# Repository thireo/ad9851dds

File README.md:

# ad9851dds
VFO based on AD9851 for future use in homemade RF Receiver
Branch testing

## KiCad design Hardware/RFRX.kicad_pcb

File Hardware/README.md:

# ad9851dds
VFO based on AD9851 for future use in homemade RF Receiver
Branch testing
revision 2 branch test?

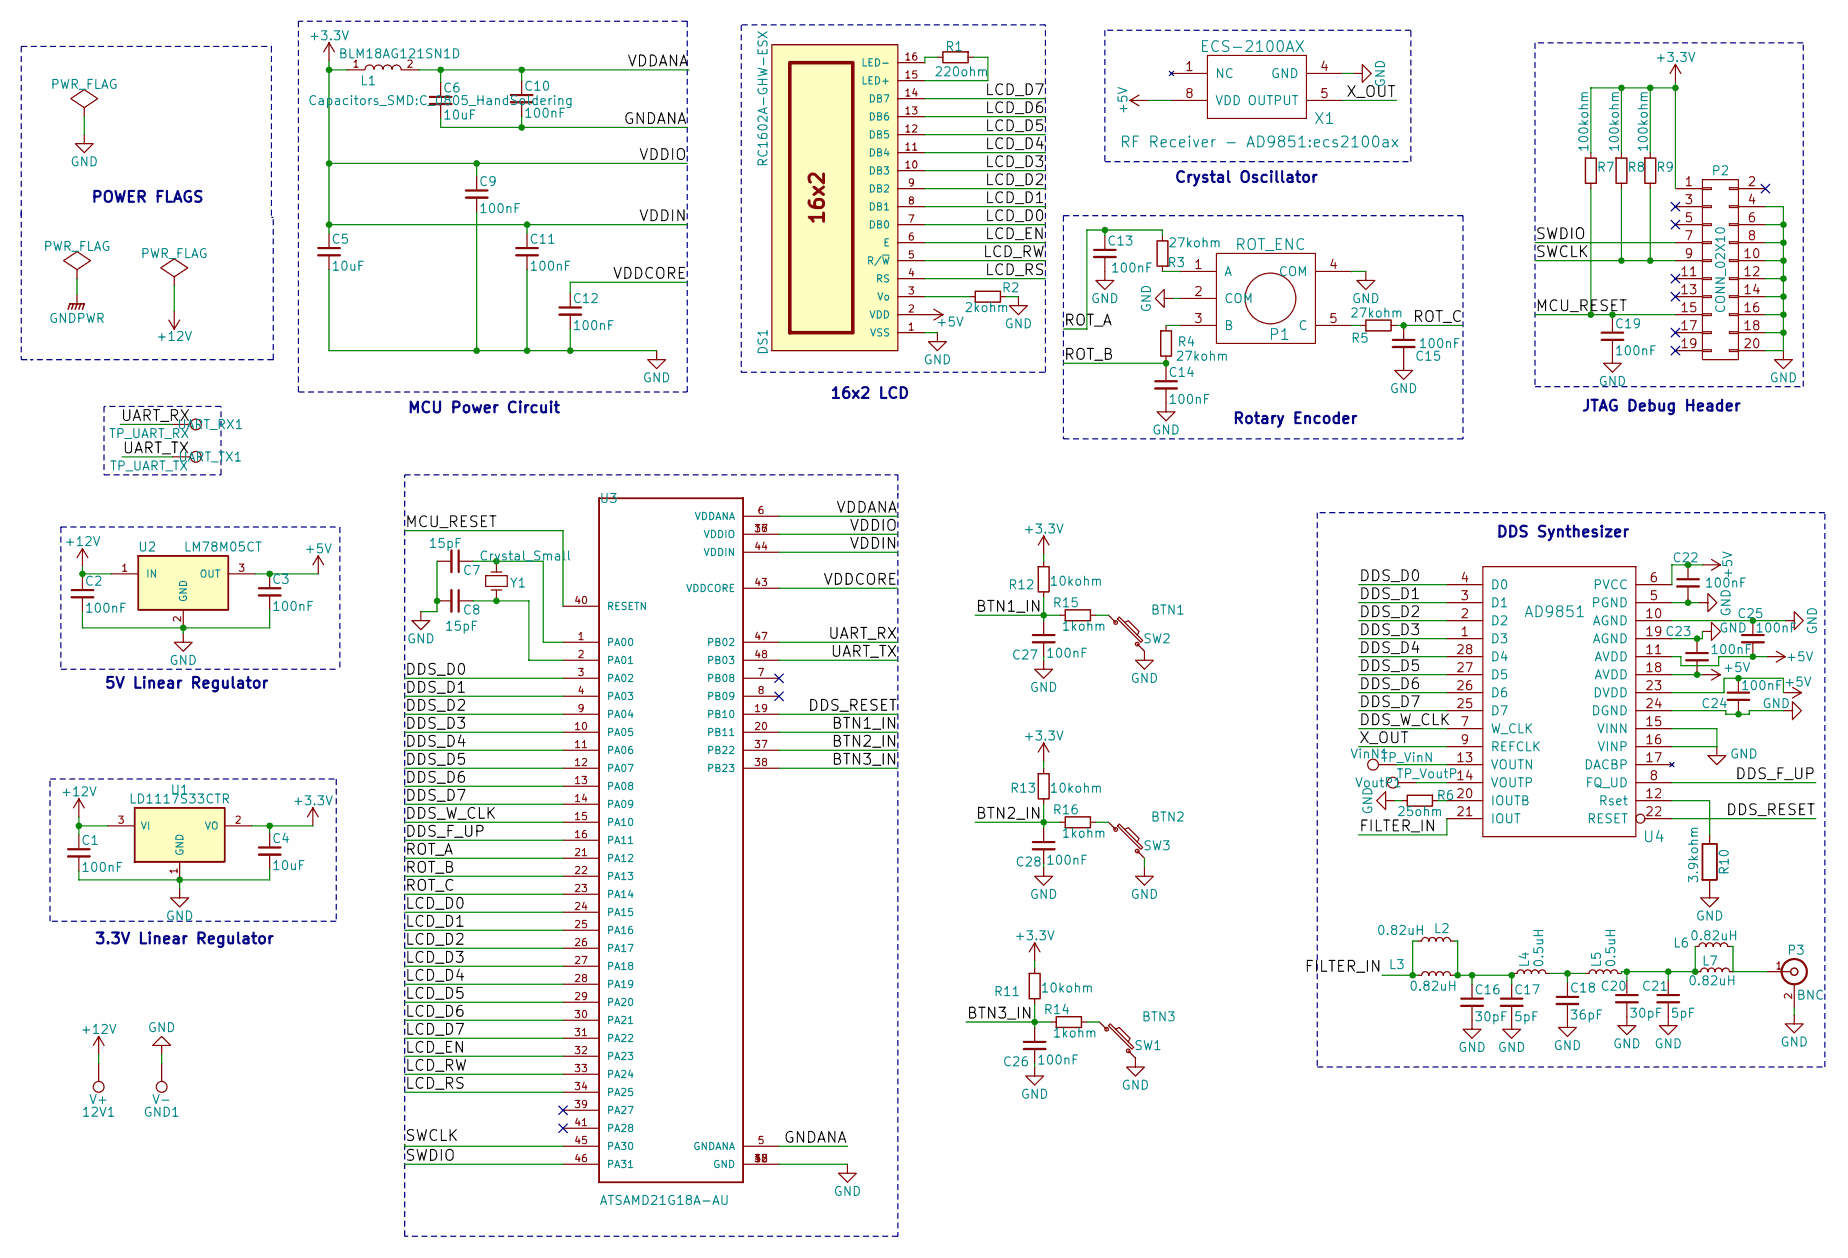
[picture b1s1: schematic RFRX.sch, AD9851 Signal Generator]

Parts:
12V1: V+; SolderWirePad_single_1-2mmDrill
C1, C2, C3, C9, C10, C11, C12, C13, C14, C15, C19, C22, C23, C24, C25, C26, C27, C28: 100nF; C_0805_HandSoldering
C4, C5, C6: 10uF; C_0805_HandSoldering
C7, C8: 15pF; C_0805_HandSoldering
C16, C20: 30pF; C_0805_HandSoldering
C17, C21: 5pF; C_0805_HandSoldering
C18: 36pF; C_0805_HandSoldering
DS1: RC1602A-GHW-ESX; Pin_Header_Straight_1x16
GND1: V-; SolderWirePad_single_1-2mmDrill
L1: BLM18AG121SN1D; R_1206_HandSoldering
L2, L3, L6, L7: 0.82uH; C_0603_HandSoldering
L4, L5: 0.5uH; C_0603_HandSoldering
P1: ROT_ENC; Pin_Header_Straight_1x05
P2: CONN_02X10; Pin_Header_Straight_2x10
P3: BNC; BNC_Socket_TYCO-AMP
R1: 220ohm; R_0805_HandSoldering
R2: 2kohm; R_0805_HandSoldering
R3, R4, R5: 27kohm; R_0805_HandSoldering
R6: 25ohm; R_0805_HandSoldering
R7, R8, R9: 100kohm; R_0805_HandSoldering
R10: 3.9kohm; R_0805_HandSoldering
R11, R12, R13: 10kohm; R_0805_HandSoldering
R14, R15, R16: 1kohm; R_0805_HandSoldering
SW1: BTN3; SolderWirePad_2x_1mmDrill
SW2: BTN1; SolderWirePad_2x_1mmDrill
SW3: BTN2; SolderWirePad_2x_1mmDrill
U1: LD1117S33CTR; SOT-223
U2: LM78M05CT; TO-220_Neutral123_Horizontal_LargePads
U3: ATSAMD21G18A-AU; TQFP-48_7x7mm_Pitch0.5mm
U4: AD9851; SSOP-28_5.3x10.2mm_Pitch0.65mm
UART_RX1: TP_UART_RX; SolderWirePad_single_1-2mmDrill
UART_TX1: TP_UART_TX; SolderWirePad_single_1-2mmDrill
VinN1: TP_VinN; SolderWirePad_single_1-2mmDrill
VoutP1: TP_VoutP; SolderWirePad_single_1-2mmDrill
X1: ECS-2100AX; ecs2100ax
Y1: Crystal_Small; XTAL320X150X90

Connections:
+3V3: C4.1, C5.1, C9.1, C11.1, L1.1, P2.1, R7.1, R8.1, R9.1, R11.1, R12.1, R13.1, U1.2 (VO), U3.17 (VDDIO), U3.36 (VDDIO), U3.44 (VDDIN)
+5V: C3.1, C22.1, C23.2, C24.1, C25.2, DS1.2 (VDD), U2.3 (OUT), U4.6 (PVCC), U4.11 (AVDD), U4.18 (AVDD), U4.23 (DVDD), X1.8 (VDD)
+12V: 12V1.1, C1.1, C2.1, U1.3 (VI), U2.1 (IN); also elsewhere on the board
/BTN1_IN: C27.1, R12.2, R15.1, U3.20 (PB11)
/BTN2_IN: C28.1, R13.2, R16.1, U3.37 (PB22)
/BTN3_IN: C26.1, R11.2, R14.1, U3.38 (PB23)
/DDS_D0: U3.3 (PA02), U4.4 (D0)
/DDS_D1: U3.4 (PA03), U4.3 (D1)
/DDS_D2: U3.9 (PA04), U4.2 (D2)
/DDS_D3: U3.10 (PA05), U4.1 (D3)
/DDS_D4: U3.11 (PA06), U4.28 (D4)
/DDS_D5: U3.12 (PA07), U4.27 (D5)
/DDS_D6: U3.13 (PA08), U4.26 (D6)
/DDS_D7: U3.14 (PA09), U4.25 (D7)
/DDS_F_UP: U3.16 (PA11), U4.8 (FQ_UD)
/DDS_RESET: U3.19 (PB10), U4.22 (RESET)
/DDS_W_CLK: U3.15 (PA10), U4.7 (W_CLK)
/FILTER_IN: L2.1, L3.1, U4.21 (IOUT)
/GNDANA: C6.2, C10.2, U3.5 (GNDANA)
/LCD_D0: DS1.7 (DB0), U3.24 (PA15)
/LCD_D1: DS1.8 (DB1), U3.25 (PA16)
/LCD_D2: DS1.9 (DB2), U3.26 (PA17)
/LCD_D3: DS1.10 (DB3), U3.27 (PA18)
/LCD_D4: DS1.11 (DB4), U3.28 (PA19)
/LCD_D5: DS1.12 (DB5), U3.29 (PA20)
/LCD_D6: DS1.13 (DB6), U3.30 (PA21)
/LCD_D7: DS1.14 (DB7), U3.31 (PA22)
/LCD_EN: DS1.6 (E), U3.32 (PA23)
/LCD_RS: DS1.4 (RS), U3.34 (PA25)
/LCD_RW: DS1.5 (R/~W), U3.33 (PA24)
/MCU_RESET: C19.1, P2.15, R7.2, U3.40 (RESETN)
/ROT_A: C13.1, R3.2, U3.21 (PA12)
/ROT_B: C14.1, R4.2, U3.22 (PA13)
/ROT_C: C15.1, R5.2, U3.23 (PA14)
/SWCLK: P2.9, R8.2, R9.2, U3.45 (PA30)
/SWDIO: P2.7, U3.46 (PA31)
/UART_RX: U3.47 (PB02), UART_RX1.1; also elsewhere on the board
/UART_TX: U3.48 (PB03), UART_TX1.1; also elsewhere on the board
/VDDANA: C6.1, C10.1, L1.2, U3.6 (VDDANA)
/VDDCORE: C12.1, U3.43 (VDDCORE)
/X_OUT: U4.9 (REFCLK), X1.5 (OUTPUT)
GND: C1.2, C2.2, C3.2, C4.2, C5.2, C7.2, C8.2, C9.2, C11.2, C12.2, C13.2, C14.2, C15.2, C16.2, C17.2, C18.2, C19.2, C20.2, C21.2, C22.2, C23.1, C24.2, C25.1, C26.2, C27.2, C28.2, DS1.1 (VSS), GND1.1, P1.2 (COM), P1.4 (COM), P2.4, P2.6, P2.8, P2.10, P2.12, P2.14, P2.16, P2.18, P2.20, P3.2 (Ext), R2.2, R6.2, R10.2, SW1.1, SW1.2, SW2.1, SW2.2, SW3.1, SW3.2, U1.1 (GND), U1.4, U2.2 (GND), U3.18 (GND), U3.35 (GND), U3.42 (GND), U4.5 (PGND), U4.10 (AGND), U4.15 (VINN), U4.16 (VINP), U4.19 (AGND), U4.24 (DGND), X1.4 (GND); also elsewhere on the board
unnamed: C7.1, U3.1 (PA00), Y1.1
unnamed: C8.1, U3.2 (PA01), Y1.2
unnamed: C16.1, C17.1, L2.2, L3.2, L4.1
unnamed: C18.1, L4.2, L5.1
unnamed: C20.1, C21.1, L5.2, L6.1, L7.1
unnamed: DS1.3 (Vo), R2.1
unnamed: DS1.15 (LED+), R1.1
unnamed: DS1.16 (LED-), R1.2
unnamed: L6.2, L7.2, P3.1 (In)
unnamed: P1.1 (A), R3.1
unnamed: P1.3 (B), R4.1
unnamed: P1.5 (C), R5.1
unnamed: R6.1, U4.20 (IOUTB)
unnamed: R10.1, U4.12 (Rset)
unnamed: R14.2, SW1.1
unnamed: R15.2, SW2.1
unnamed: R16.2, SW3.1
unnamed 70: U4.13 (VOUTN), VinN1.1; also elsewhere on the board
unnamed 71: U4.14 (VOUTP), VoutP1.1; also elsewhere on the board

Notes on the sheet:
DDS Synthesizer
Crystal Oscillator
16x2 LCD
MCU Power Circuit
POWER FLAGS
Rotary Encoder
JTAG Debug Header
3.3V Linear Regulator
5V Linear Regulator

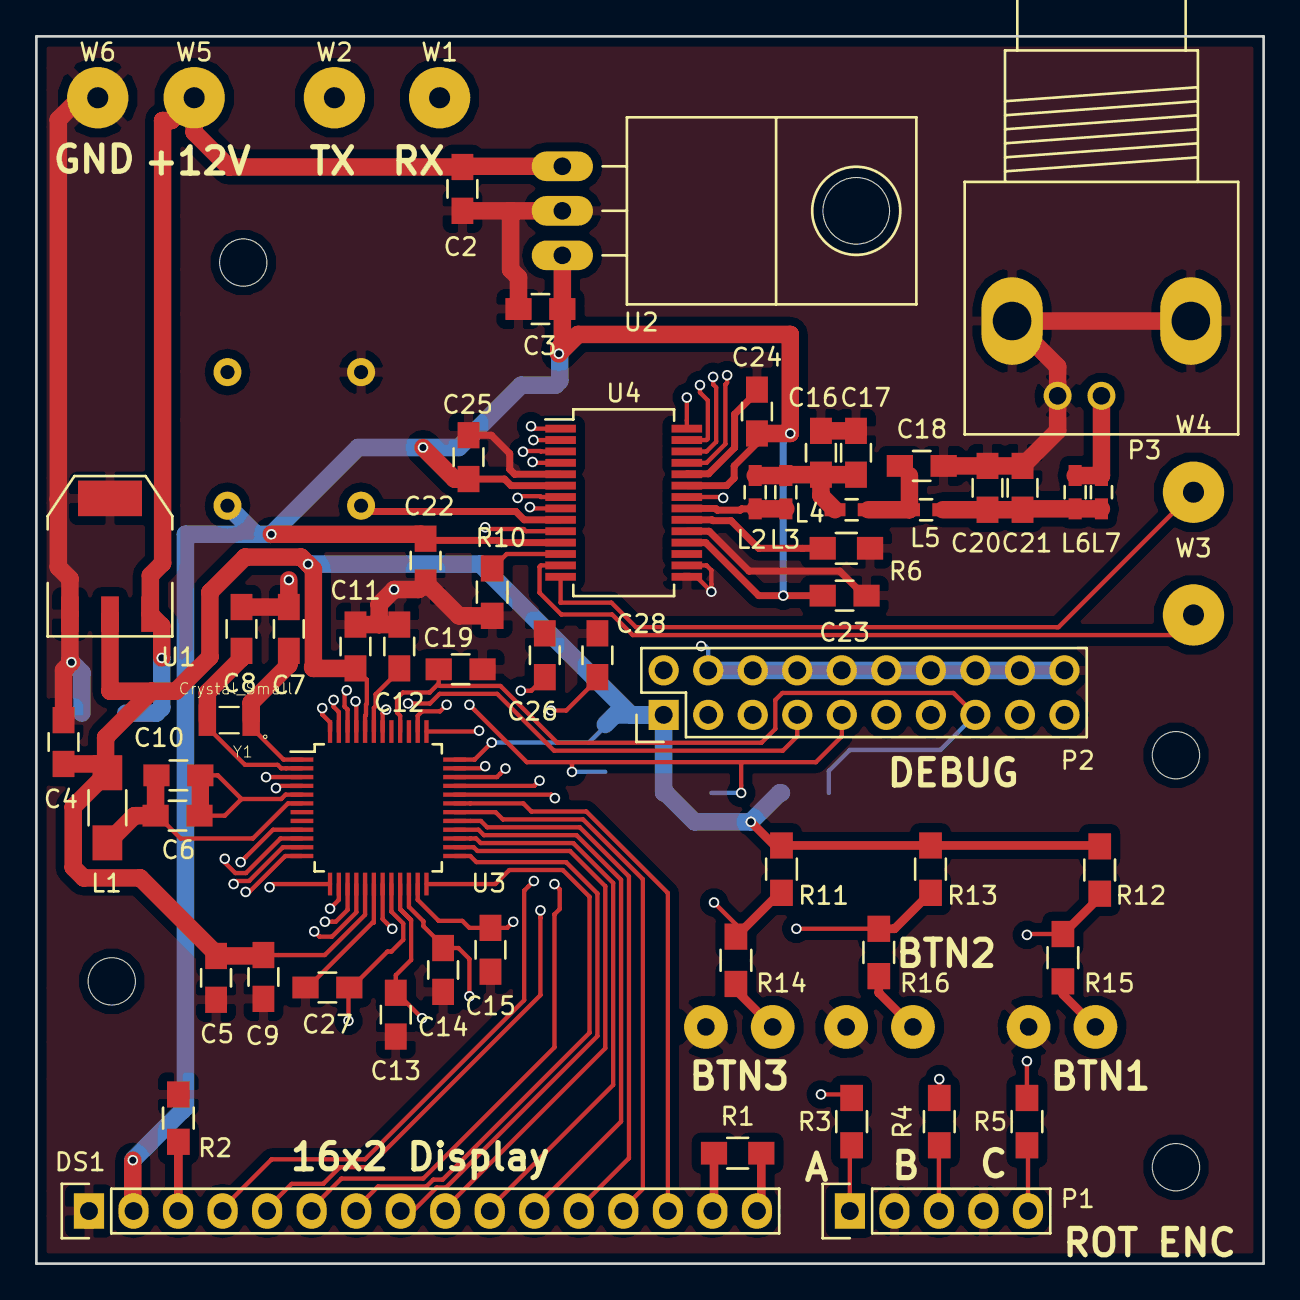
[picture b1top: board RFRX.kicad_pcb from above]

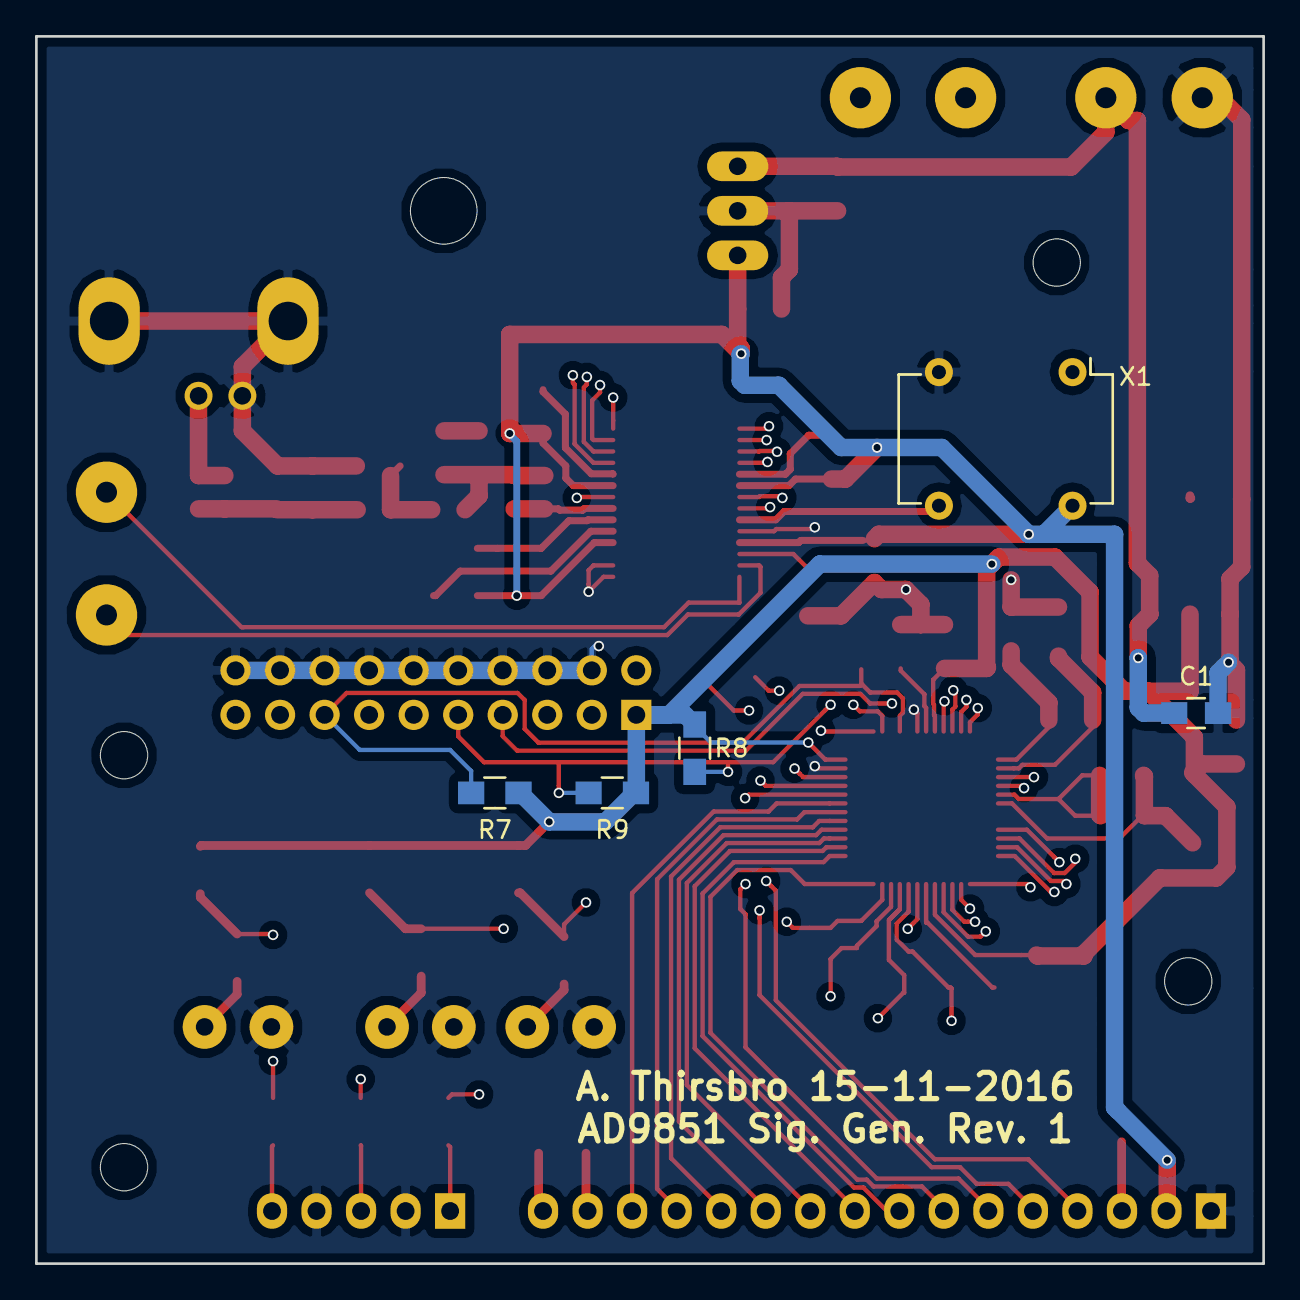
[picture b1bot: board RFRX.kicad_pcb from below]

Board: 4 copper layers, 70.0 x 70.0 mm, 70 parts (5 on the bottom side), 61 nets.

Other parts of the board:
W1: TP_UART_RX; SolderWirePad_single_1-2mmDrill
W2: TP_UART_TX; SolderWirePad_single_1-2mmDrill
W3: TP_VinN; SolderWirePad_single_1-2mmDrill
W4: TP_VoutP; SolderWirePad_single_1-2mmDrill
W5: V+; SolderWirePad_single_1-2mmDrill
W6: V-; SolderWirePad_single_1-2mmDrill

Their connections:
+12V: W5.1; also elsewhere on the board
/UART_RX: W1.1; also elsewhere on the board
/UART_TX: W2.1; also elsewhere on the board
GND: W6.1; also elsewhere on the board
unnamed 70: W3.1; also elsewhere on the board
unnamed 71: W4.1; also elsewhere on the board

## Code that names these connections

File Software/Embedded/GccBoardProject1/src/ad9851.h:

/*
 * ad9851.h
 *
 * Created: 27-12-2016 23:20:55
 *  Author: Andreas
 */ 


#ifndef AD9851_H_
#define AD9851_H_

#include "asf.h"

#define CLOCK_IN 20000000
#define CLOCK_MULTIPLIER 6
#define MAX_WORD 4294967295
#define CLOCK_WORD_RATIO (MAX_WORD/(CLOCK_IN*CLOCK_MULTIPLIER))

#define DDS_D0 PIN_PA02
#define DDS_D1 PIN_PA03
#define DDS_D2 PIN_PA04
#define DDS_D3 PIN_PA05
#define DDS_D4 PIN_PA06
#define DDS_D5 PIN_PA07
#define DDS_D6 PIN_PA08
#define DDS_D7 PIN_PA09
#define DDS_W_CLK PIN_PA10
#define DDS_F_UP PIN_PA11
#define DDS_RESET PIN_PB10

void ad9851_init(void);
unsigned int calc_word(double freq);
void put_data_byte(uint8_t word);
void send_word(uint32_t word);


#endif /* AD9851_H_ */

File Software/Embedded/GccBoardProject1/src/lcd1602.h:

/*
 * lcd1602.h
 *
 * Created: 27-12-2016 14:42:19
 *  Author: Andreas
 */ 


#ifndef LCD1602_H_
#define LCD1602_H_

#include "asf.h"

#define LCD_D0 PIN_PA15 //IOPIN_CREATE_PIN(PORTA,PIN_PA15)
#define LCD_D1 PIN_PA16 //IOPIN_CREATE_PIN(PORTA,PIN_PA16)
#define LCD_D2 PIN_PA17 //IOPIN_CREATE_PIN(PORTA,PIN_PA17)
#define LCD_D3 PIN_PA18 //IOPIN_CREATE_PIN(PORTA,PIN_PA18)
#define LCD_D4 PIN_PA19 //IOPIN_CREATE_PIN(PORTA,PIN_PA19)
#define LCD_D5 PIN_PA20 //IOPIN_CREATE_PIN(PORTA,PIN_PA20)
#define LCD_D6 PIN_PA21 //IOPIN_CREATE_PIN(PORTA,PIN_PA21)
#define LCD_D7 PIN_PA22 //IOPIN_CREATE_PIN(PORTA,PIN_PA22)

#define LCD_EN PIN_PA23 //IOPIN_CREATE_PIN(PORTA,PIN_PA23)
#define LCD_RW PIN_PA24 //IOPIN_CREATE_PIN(PORTA,PIN_PA24)
#define LCD_RS PIN_PA25 //IOPIN_CREATE_PIN(PORTA,PIN_PA25)

#define LCD_CMD_CLEAR_HOME 0x01
#define LCD_CMD_CLEAR_SET_CSR 0x06
#define LCD_CMD_CLEAR_TURN_ON_DISP 0x0C
#define LCD_CMD_CLEAR_SCREEN 0x01
#define LCD_CMD_MOVE_CURSOR_LEFT 0x10
#define LCD_CMD_MOVE_CURSOR_RIGHT 0x14
#define LCD_CMD_MOVE_DISPLAY_LEFT 0x18
#define LCD_CMD_MOVE_DISPLAY_RIGHT 0x1C


void configure_lcd_pins(void);
void lcd_init(void);
void lcd_send_string(char* string);
void lcd_data(uint8_t data);
void lcd_cmd(uint8_t command);
void lcd_clear_screen(void);
void lcd_set_line(unsigned char line);

void lcd_disp_freq(int freq);
void printfcomma2 (int n);
void printnumberswiththousandsseparatorcomma(uint32_t n);
#endif /* LCD1602_H_ */

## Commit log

2017-01-16 Update README.md
    Will this branch carry my weight?
2017-01-16 Revision 1
    Base of all future operations
2017-01-16 Changed file structure
